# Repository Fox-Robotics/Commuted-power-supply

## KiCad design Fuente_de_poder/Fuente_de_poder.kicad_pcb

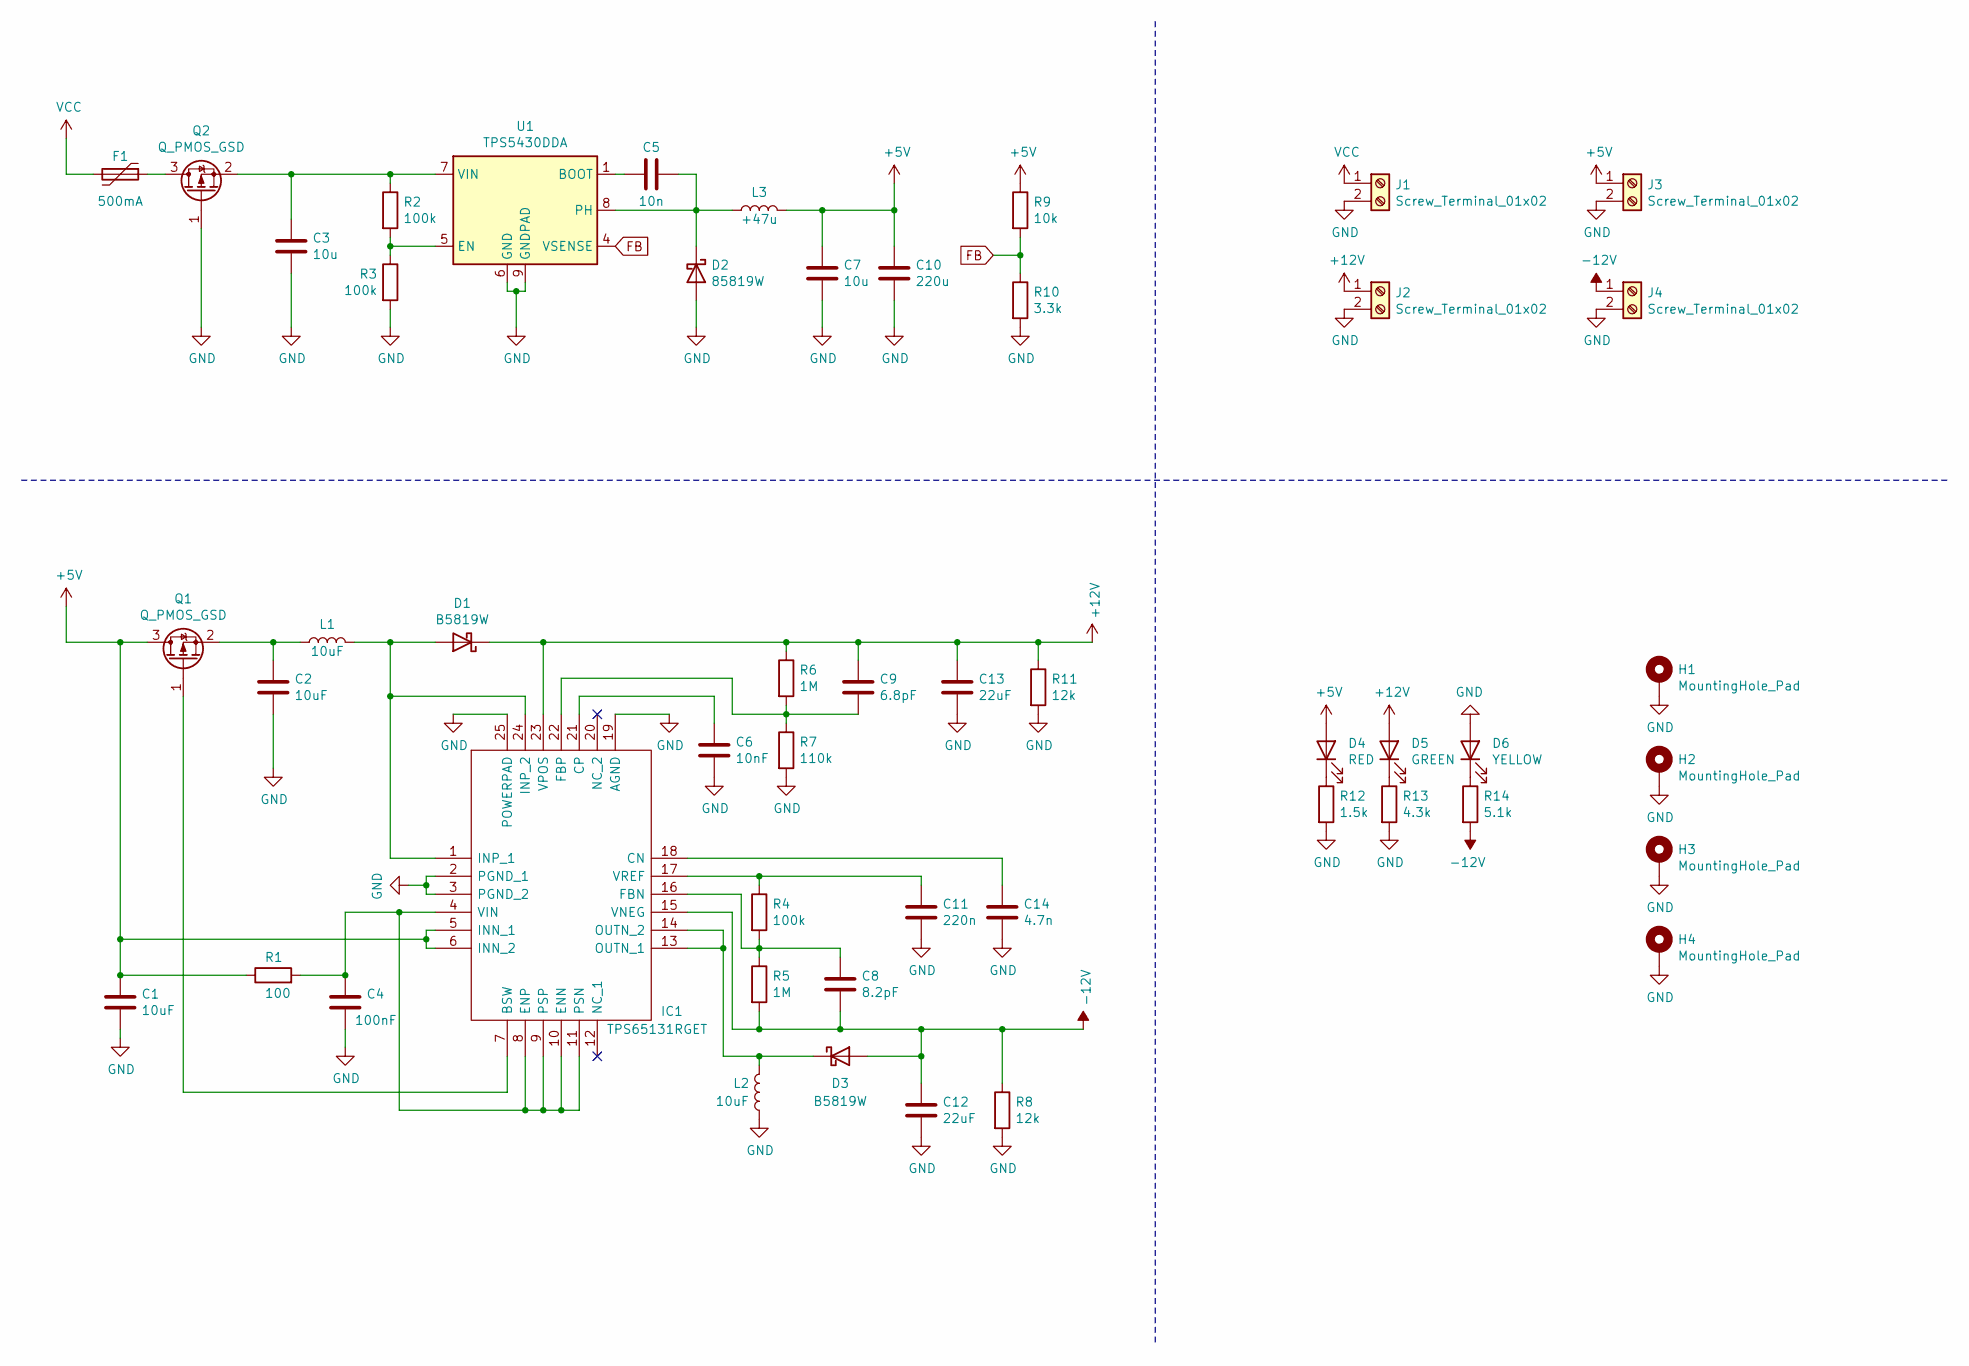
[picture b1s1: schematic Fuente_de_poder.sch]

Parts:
C1, C2: 10uF; C_1206_3216Metric_Pad1.33x1.80mm_HandSolder
C3: 10u; CP_Elec_5x5.9
C4: 100nF; C_0603_1608Metric_Pad1.08x0.95mm_HandSolder
C5: 10n; C_0603_1608Metric_Pad1.08x0.95mm_HandSolder
C6: 10nF; C_0805_2012Metric_Pad1.18x1.45mm_HandSolder
C7: 10u; C_0603_1608Metric_Pad1.08x0.95mm_HandSolder
C8: 8.2pF; C_0402_1005Metric_Pad0.74x0.62mm_HandSolder
C9: 6.8pF; C_0805_2012Metric_Pad1.18x1.45mm_HandSolder
C10: 220u; CAP_10TPB220M
C11: 220n; C_0603_1608Metric_Pad1.08x0.95mm_HandSolder
C12, C13: 22uF; C_1210_3225Metric_Pad1.33x2.70mm_HandSolder
C14: 4.7n; C_2220_5650Metric_Pad1.97x5.40mm_HandSolder
D1, D3: B5819W; D_SOD-123F
D2: 85819W; D_SOD-123F
D4: RED; LED_0805_2012Metric_Pad1.15x1.40mm_HandSolder
D5: GREEN; LED_0805_2012Metric_Pad1.15x1.40mm_HandSolder
D6: YELLOW; LED_0805_2012Metric_Pad1.15x1.40mm_HandSolder
F1: 500mA; Fuse_0805_2012Metric_Pad1.15x1.40mm_HandSolder
H1, H2, H3, H4: MountingHole_Pad; MountingHole_4.3mm_M4_DIN965_Pad
IC1: TPS65131RGET; QFN50P400X400X100-25N-D; Manufacturer_Part_Number TPS65131RGET; Mouser Part Number 595-TPS65131RGET
J1, J2, J3, J4: Screw_Terminal_01x02; TerminalBlock_Phoenix_PT-1,5-2-5.0-H_1x02_P5.00mm_Horizontal
L1, L2: 10uF; L_6.3x6.3_H3
L3: +47u; L_0805_2012Metric_Pad1.15x1.40mm_HandSolder
Q1, Q2: Q_PMOS_GSD; SOT23
R1: 100; R_0805_2012Metric_Pad1.20x1.40mm_HandSolder
R2, R3, R4: 100k; R_0805_2012Metric_Pad1.20x1.40mm_HandSolder
R5, R6: 1M; R_0805_2012Metric_Pad1.20x1.40mm_HandSolder
R7: 110k; R_0805_2012Metric_Pad1.20x1.40mm_HandSolder
R8, R11: 12k; R_0805_2012Metric_Pad1.20x1.40mm_HandSolder
R9: 10k; R_0805_2012Metric_Pad1.20x1.40mm_HandSolder
R10: 3.3k; R_0805_2012Metric_Pad1.20x1.40mm_HandSolder
R12: 1.5k; R_0805_2012Metric_Pad1.20x1.40mm_HandSolder
R13: 4.3k; R_0805_2012Metric_Pad1.20x1.40mm_HandSolder
R14: 5.1k; R_0805_2012Metric_Pad1.20x1.40mm_HandSolder
U1: TPS5430DDA; TI_SO-PowerPAD-8_ThermalVias

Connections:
+5V: C1.1, C7.1, C10.1, D4.2 (A), IC1.5 (INN_1), IC1.6 (INN_2), J3.1, L3.2, Q1.3 (D), R1.1, R9.1
+12V: C9.1, C13.1, D1.1 (K), D5.2 (A), IC1.23 (VPOS), J2.1, R6.1, R11.1
-12V: C8.2, C12.1, D3.2 (A), IC1.15 (VNEG), J4.1, R5.2, R8.1, R14.2
FB: R9.2, R10.1, U1.4 (VSENSE)
GND: C1.2, C2.2, C3.2, C4.2, C6.2, C7.2, C10.2, C11.2, C12.2, C13.2, C14.2, D2.2 (A), D6.2 (A), H1.1, H2.1, H3.1, H4.1, IC1.2 (PGND_1), IC1.3 (PGND_2), IC1.19 (AGND), IC1.25 (POWERPAD), J1.2, J2.2, J3.2, J4.2, L2.1, Q2.1 (G), R3.2, R7.2, R8.2, R10.2, R11.2, R12.2, R13.2, U1.6 (GND), U1.9 (GNDPAD)
unnamed: C2.1, L1.1, Q1.2 (S)
unnamed: C3.1, Q2.2 (S), R2.1, U1.7 (VIN)
unnamed: C4.1, IC1.4 (VIN), IC1.8 (ENP), IC1.9 (PSP), IC1.10 (ENN), IC1.11 (PSN), R1.2
unnamed: C5.1, D2.1 (K), L3.1, U1.8 (PH)
unnamed: C5.2, U1.1 (BOOT)
unnamed: C6.1, IC1.21 (CP)
unnamed: C8.1, IC1.16 (FBN), R4.2, R5.1
unnamed: C9.2, IC1.22 (FBP), R6.2, R7.1
unnamed: C11.1, IC1.17 (VREF), R4.1
unnamed: C14.1, IC1.18 (CN)
unnamed: D1.2 (A), IC1.1 (INP_1), IC1.24 (INP_2), L1.2
unnamed: D3.1 (K), IC1.13 (OUTN_1), IC1.14 (OUTN_2), L2.2
unnamed: D4.1 (K), R12.1
unnamed: D5.1 (K), R13.1
unnamed: D6.1 (K), R14.1
unnamed: F1.1, Q2.3 (D)
unnamed: IC1.7 (BSW), Q1.1 (G)
unnamed: R2.2, R3.1, U1.5 (EN)
VCC: F1.2, J1.1

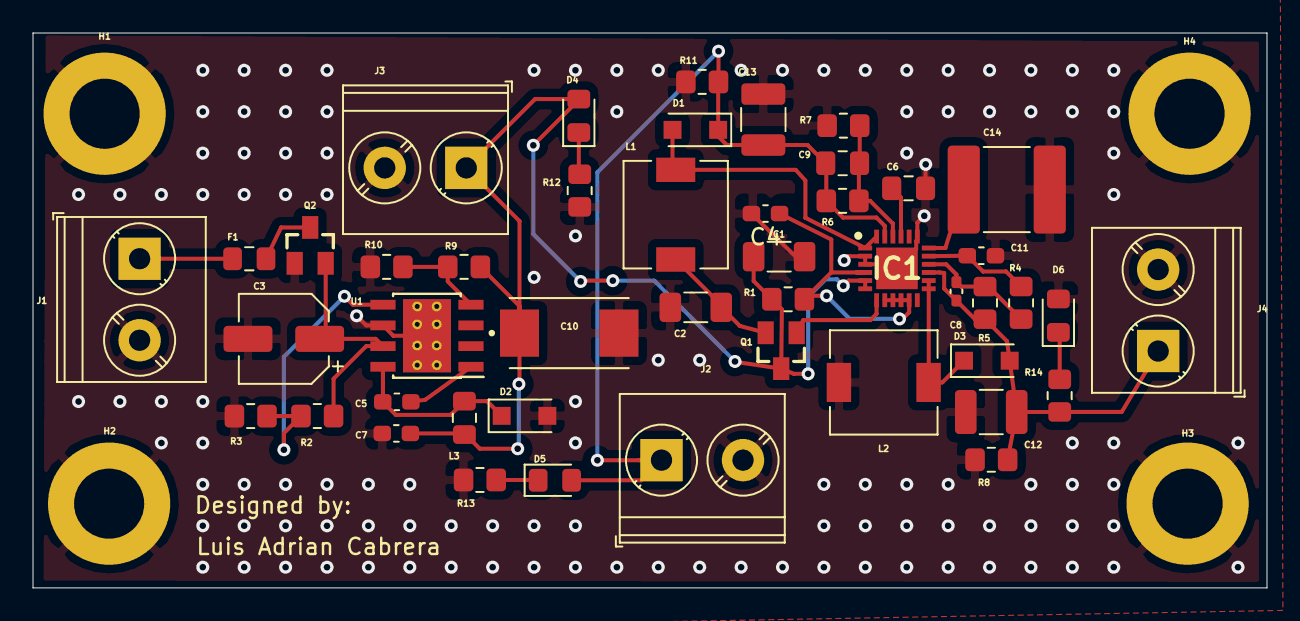
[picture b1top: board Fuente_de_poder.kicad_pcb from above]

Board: 2 copper layers, 75.7 x 34.0 mm, 50 parts (0 on the bottom side), 24 nets.
